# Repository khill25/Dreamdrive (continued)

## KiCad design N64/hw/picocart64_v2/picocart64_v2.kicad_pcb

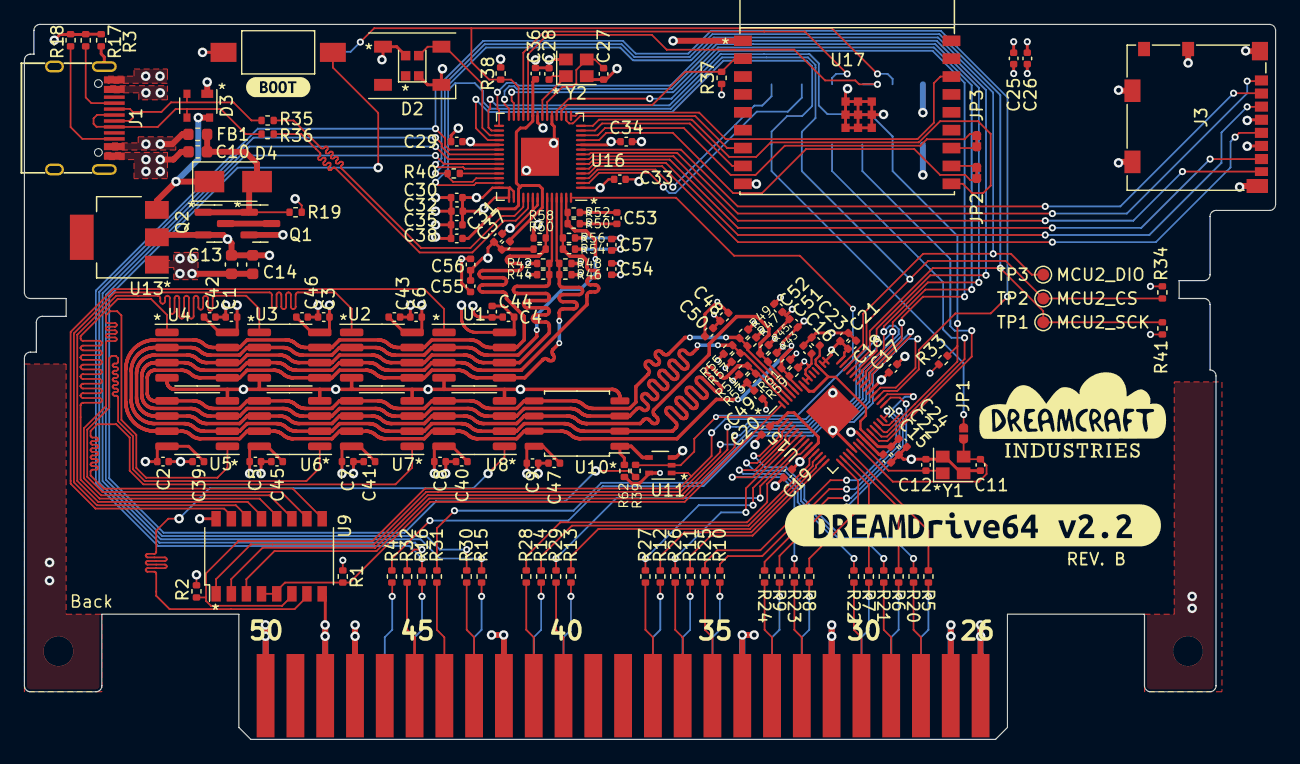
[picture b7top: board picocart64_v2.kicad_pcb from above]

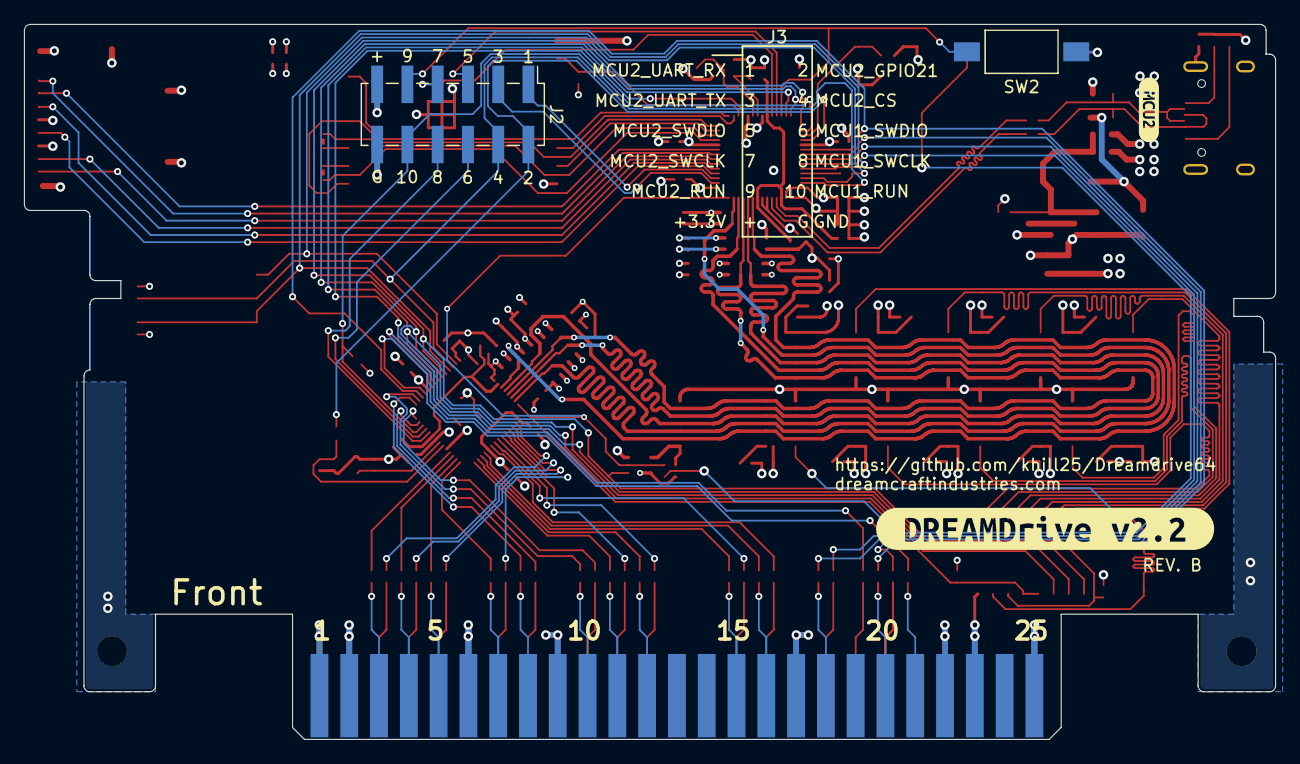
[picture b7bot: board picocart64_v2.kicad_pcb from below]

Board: 4 copper layers, 105.0 x 60.0 mm, 159 parts (5 on the bottom side), 121 nets.

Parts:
C1, C2, C3, C4, C5, C6, C7, C8, C9, C15, C16, C17, C18, C19, C20, C22, C23, C26, C29, C30, C31, C32, C33, C34, C36, C37, C48, C49, C50, C51, C52, C53, C54, C55, C56, C57: 100n; C_0402_1005Metric
C10, C13, C14: 10u; C_0603_1608Metric
C11, C12, C27, C28: 12p; C_0402_1005Metric
C21, C24, C25, C35, C38, C39, C40, C41, C42, C43, C44, C45, C46, C47: 1u; C_0402_1005Metric
D1: WS2812B-2020
D2: WS2812B; LED_WS2812B_PLCC4_5.0x5.0mm_P3.2mm
D3: DRTR5V0U2SR-7; SOT-143
D4: D_Small; D_SMA
FB1: Ferrite; L_0603_1608Metric
J1: USB_C_Receptacle_USB2.0; USB_C_Receptacle_GT-USB-7010
J2: Conn_02x06_Odd_Even; PinHeader_2x06_P2.54mm_Vertical_SMD
J3: Micro_SD_Card_Det; microSD_HC_Molex_104031-0811
JP1: SolderJumper_2_Open; SolderJumper-2_Small_Open
JP2, JP3: SolderJumper_2_Bridged; SolderJumper-2_Small_Closed
Q1, Q2: FDN340P; SOT-23
R1, R2, R33, R34, R62: 10K; R_0402_1005Metric
R3: 100k; R_0402_1005Metric
R4, R5, R6, R7, R8, R9, R10, R11, R12, R13, R14, R15, R16, R20, R21, R22, R23, R24, R25, R26, R27, R28, R29, R30, R31, R32, R35, R36: 22R; R_0402_1005Metric
R17, R18: 5k1; R_0402_1005Metric
R19, R37, R38, R41: 10k; R_0402_1005Metric
R39: 1K; R_0402_1005Metric
R40: 470R; R_0402_1005Metric
R42, R43, R44, R45, R46, R47, R48, R49, R50, R51, R52, R53, R54, R55, R56, R57, R58, R59, R60, R61: R; R_0402_1005Metric
SW1: BootButton; SW_SPST_FSMSM
SW2: ResetButton; SW_SPST_FSMSM
TP1: TP_MCU2_SCK; TestPoint_Pad_D1.0mm
TP2: TP_MCU2_CS; TestPoint_Pad_D1.0mm
TP3: TP_MCU2_DIO; TestPoint_Pad_D1.0mm
U1, U2, U3, U4, U5, U6, U7, U8: APS6404L-3SQR; SOP-8_3.76x4.96mm_P1.27mm
U9: SN74LVC138AQDRQ1; SOP-16_4.4x10.4mm_P1.27mm
U10: W25Q128JVS; SOIC-8_5.23x5.23mm_P1.27mm
U11: 74LVC1G125GW; SOT-353_SC-70-5
U13: AZ1117-3.3; SOT-223
U14: N64-Cartridge; N64-Connector
U15, U16: RP2040; QFN-56_EP_7x7_Pitch0.4mm
U17: ESP32-C3-WROOM-02
Y1, Y2: 12MHz 10ppm; Crystal_SMD_2520-4Pin_2.5x2.0mm
kibuzzard-62F8E97D: G***; kibuzzard-62F8E97D
kibuzzard-62F95F09: G***; kibuzzard-62F95F09
kibuzzard-63B14A32: G***; kibuzzard-63B14A32
kibuzzard-63B14B13: G***; kibuzzard-63B14B13

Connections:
+3V3: C1.1, C2.1, C3.1, C4.1, C5.1, C6.1, C7.1, C8.1, C9.1, C13.1, C14.1, C15.1, C16.1, C17.1, C18.1, C19.1, C20.1, C21.1, C25.1, C26.1, C29.1, C30.1, C31.1, C32.1, C33.1, C34.1, C35.1, C39.1, C40.1, C41.1, C42.1, C43.1, C44.1, C45.1, C46.1, C47.1, C48.1, C49.1, C50.1, C51.1, C52.1, C53.1, C54.1, C55.1, C56.1, C57.1, D1.4 (VDD), D2.1 (VDD), J2.11, J3.4 (VDD), Q2.2 (S), R1.1, R34.2, R38.1, R41.1, R42.2, R43.2, R46.2, R47.2, R50.2, R51.2, R54.2, R55.2, R58.2, R59.2, R62.2, U1.8 (VCC), U2.8 (VCC), U3.8 (VCC), U4.8 (VCC), U5.8 (VCC), U6.8 (VCC), U7.8 (VCC), U8.8 (VCC), U9.16 (VCC), U10.8 (VCC), U11.5 (VCC), U13.2 (VO), U15.1 (IOVDD), U15.10 (IOVDD), U15.22 (IOVDD), U15.33 (IOVDD), U15.42 (IOVDD), U15.43 (ADC_AVDD), U15.44 (VREG_VIN), U15.48 (USB_VDD), U15.49 (IOVDD), U16.1 (IOVDD), U16.10 (IOVDD), U16.22 (IOVDD), U16.33 (IOVDD), U16.42 (IOVDD), U16.43 (ADC_AVDD), U16.44 (VREG_VIN), U16.48 (USB_VDD), U16.49 (IOVDD), U17.1 (3V3)
/Mainboard/AD0: R20.2, U15.2 (GPIO0)
/Mainboard/AD0': R20.1, U14.28 (AD0)
/Mainboard/AD1: R21.2, U15.3 (GPIO1)
/Mainboard/AD1': R21.1, U14.29 (AD1)
/Mainboard/AD2: R22.2, U15.4 (GPIO2)
/Mainboard/AD2': R22.1, U14.30 (AD2)
/Mainboard/AD3: R23.2, U15.5 (GPIO3)
/Mainboard/AD3': R23.1, U14.32 (AD3)
/Mainboard/AD4: R26.2, U15.6 (GPIO4)
/Mainboard/AD4': R26.1, U14.36 (AD4)
/Mainboard/AD5: R27.2, U15.7 (GPIO5)
/Mainboard/AD5': R27.1, U14.37 (AD5)
/Mainboard/AD6: R29.2, U15.8 (GPIO6)
/Mainboard/AD6': R29.1, U14.40 (AD6)
/Mainboard/AD7: R28.2, U15.9 (GPIO7)
/Mainboard/AD7': R28.1, U14.41 (AD7)
/Mainboard/AD8: R14.1, U15.11 (GPIO8)
/Mainboard/AD8': R14.2, U14.16 (AD8)
/Mainboard/AD9: R13.1, U15.12 (GPIO9)
/Mainboard/AD9': R13.2, U14.15 (AD9)
/Mainboard/AD10: R12.1, U15.13 (GPIO10)
/Mainboard/AD10': R12.2, U14.12 (AD10)
/Mainboard/AD11: R11.1, U15.14 (GPIO11)
/Mainboard/AD11': R11.2, U14.11 (AD11)
/Mainboard/AD12: R8.1, U15.15 (GPIO12)
/Mainboard/AD12': R8.2, U14.7 (AD12)
/Mainboard/AD13: R7.1, U15.16 (GPIO13)
/Mainboard/AD13': R7.2, U14.5 (AD13)
/Mainboard/AD14: R6.1, U15.17 (GPIO14)
/Mainboard/AD14': R6.2, U14.4 (AD14)
/Mainboard/AD15: R5.1, U15.18 (GPIO15)
/Mainboard/AD15': R5.2, U14.3 (AD15)
/Mainboard/ALEH: R25.2, U15.28 (GPIO17)
/Mainboard/ALEH': R25.1, U14.35 (ALEH)
/Mainboard/ALEL: R24.2, U15.27 (GPIO16)
/Mainboard/ALEL': R24.1, U14.33 (ALEL)
/Mainboard/CIC_DCLK: R30.2, U16.37 (GPIO25)
/Mainboard/CIC_DCLK': R30.1, U14.43 (CIC_DCLK)
/Mainboard/CIC_DIO: R15.1, U16.36 (GPIO24)
/Mainboard/CIC_DIO': R15.2, U14.18 (CIC_DIO)
/Mainboard/DEMUX_A0: U9.1 (A0), U15.35 (GPIO23), U16.18 (GPIO15)
/Mainboard/DEMUX_A1: U9.2 (A1), U15.36 (GPIO24), U16.27 (GPIO16)
/Mainboard/DEMUX_A2: U9.3 (A2), U15.37 (GPIO25), U16.28 (GPIO17)
/Mainboard/DEMUX_IE: R2.2, U9.6 (E3), U11.1 (~OE), U15.38 (GPIO26), U16.29 (GPIO18)
/Mainboard/ESP32_CS: U16.15 (GPIO12), U17.16 (GPIO2/ADC1_CH2)
/Mainboard/ESP32_D0_TX: JP2.2 (B), U16.11 (GPIO8)
/Mainboard/ESP32_D1_RX: JP3.2 (B), U16.12 (GPIO9)
/Mainboard/ESP32_D2_G9: U16.13 (GPIO10), U17.8 (GPIO9)
/Mainboard/ESP32_D3: U16.14 (GPIO11), U17.10 (GPIO10)
/Mainboard/ESP32_EN: R37.2, U16.17 (GPIO14), U17.2 (EN/CHIP_PU)
/Mainboard/ESP32_SCK: U16.16 (GPIO13), U17.7 (GPIO8)
/Mainboard/LED: D1.3 (DIN), D2.4 (DIN), U16.31 (GPIO20)
/Mainboard/MCU1_RUN: J2.10, R33.2, U15.26 (RUN), U16.30 (GPIO19)
/Mainboard/MCU1_SWCLK: J2.8, U15.24 (SWCLK)
/Mainboard/MCU1_SWDIO: J2.6, U15.25 (SWDIO)
/Mainboard/MCU1_XIN: C11.2, JP1.2 (B), U15.20 (XIN), Y1.3
/Mainboard/MCU1_XOUT: C12.2, U15.21 (XOUT), Y1.1
/Mainboard/MCU2_CS: J2.4, R34.1, TP2.1, U15.40 (GPIO28), U16.41 (GPIO29)
/Mainboard/MCU2_DIO: R40.2, TP3.1, U15.41 (GPIO29), U16.40 (GPIO28)
/Mainboard/MCU2_G27: R40.1, U16.39 (GPIO27)
/Mainboard/MCU2_GPIO21: J2.2, JP1.1 (A), U16.32 (GPIO21)
/Mainboard/MCU2_RUN: J2.9, R38.2, SW2.1, U16.26 (RUN)
/Mainboard/MCU2_SCK: R41.2, TP1.1, U15.39 (GPIO27), U16.38 (GPIO26)
/Mainboard/MCU2_SWCLK: J2.7, U16.24 (SWCLK)
/Mainboard/MCU2_SWDIO: J2.5, U16.25 (SWDIO)
/Mainboard/MCU2_UART_RX: J2.1, U16.3 (GPIO1)
/Mainboard/MCU2_UART_TX: J2.3, U16.2 (GPIO0)
/Mainboard/MCU2_USB_D+: D3.3 (I/O2), J1.A6 (D+), J1.B6 (D+), R36.1
/Mainboard/MCU2_USB_D-: D3.2 (I/O1), J1.A7 (D-), J1.B7 (D-), R35.1
/Mainboard/MCU2_XIN: C27.2, U16.20 (XIN), Y2.3
/Mainboard/MCU2_XOUT: C28.2, U16.21 (XOUT), Y2.1
/Mainboard/N64_VCC: Q1.2 (S), U14.9 (VCC), U14.17 (VCC), U14.34 (VCC), U14.42 (VCC)
/Mainboard/SD_CLK: J3.5 (CLK), U16.4 (GPIO2)
/Mainboard/SD_CMD: J3.3 (CMD), U16.5 (GPIO3)
/Mainboard/SD_DAT0: J3.7 (DAT0), U16.6 (GPIO4)
/Mainboard/SD_DAT1: J3.8 (DAT1), U16.7 (GPIO5)
/Mainboard/SD_DAT2: J3.1 (DAT2), U16.8 (GPIO6)
/Mainboard/SD_DAT3: J3.2 (DAT3/CD), U16.9 (GPIO7)
/Mainboard/SI_DAT: R4.1, U15.32 (GPIO21)
/Mainboard/SI_DAT': R4.2, U14.21 (SI_DAT)
/Mainboard/SSI_SCLK: R42.1, R43.1, R44.2, R45.2, U1.6 (SCLK), U2.6 (SCLK), U3.6 (SCLK), U4.6 (SCLK), U5.6 (SCLK), U6.6 (SCLK), U7.6 (SCLK), U8.6 (SCLK), U10.6 (CLK), U15.52 (QSPI_SCLK), U16.52 (QSPI_SCLK)
/Mainboard/SSI_SD0: R46.1, R47.1, R48.2, R49.2, U1.5 (SI/SIO), U2.5 (SI/SIO), U3.5 (SI/SIO), U4.5 (SI/SIO), U5.5 (SI/SIO), U6.5 (SI/SIO), U7.5 (SI/SIO), U8.5 (SI/SIO), U10.5 (DI(IO0)), U15.53 (QSPI_SD0), U16.53 (QSPI_SD0)
/Mainboard/SSI_SD1: R50.1, R51.1, R52.2, R53.2, U1.2 (SO/SIO), U2.2 (SO/SIO), U3.2 (SO/SIO), U4.2 (SO/SIO), U5.2 (SO/SIO), U6.2 (SO/SIO), U7.2 (SO/SIO), U8.2 (SO/SIO), U10.2 (DO(IO1)), U15.55 (QSPI_SD1), U16.55 (QSPI_SD1)
/Mainboard/SSI_SD2: R54.1, R55.1, R56.2, R57.2, U1.3 (SIO2), U2.3 (SIO2), U3.3 (SIO2), U4.3 (SIO2), U5.3 (SIO2), U6.3 (SIO2), U7.3 (SIO2), U8.3 (SIO2), U10.3 (IO2), U15.54 (QSPI_SD2), U16.54 (QSPI_SD2)
/Mainboard/SSI_SD3: R58.1, R59.1, R60.2, R61.2, U1.7 (SIO3), U2.7 (SIO3), U3.7 (SIO3), U4.7 (SIO3), U5.7 (SIO3), U6.7 (SIO3), U7.7 (SIO3), U8.7 (SIO3), U10.7 (IO3), U15.51 (QSPI_SD3), U16.51 (QSPI_SD3)
/Mainboard/VBUS': FB1.1, J1.A4 (VBUS), J1.A9 (VBUS), J1.B4 (VBUS), J1.B9 (VBUS)
/Mainboard/~COLD_RESET': R16.2, U14.20 (~COLD_RESET)
/Mainboard/~COLD_RESET: R16.1, U15.31 (GPIO20), U16.34 (GPIO22)
/Mainboard/~INT1': R31.1, U14.44 (~INT1)
/Mainboard/~INT1: R31.2, U15.34 (GPIO22)
/Mainboard/~NMI': R32.1, U14.45 (~NMI)
/Mainboard/~NMI: R32.2, U16.35 (GPIO23)
/Mainboard/~READ': R10.2, U14.10 (~READ)
/Mainboard/~READ: R10.1, U15.30 (GPIO19)
/Mainboard/~WRITE': R9.2, U14.8 (~WRITE)
/Mainboard/~WRITE: R9.1, U15.29 (GPIO18)
/PSRAM Array/CS1: U1.1 (~CE), U9.15 (O0)
/PSRAM Array/CS2: U2.1 (~CE), U9.14 (O1)
/PSRAM Array/CS3: U3.1 (~CE), U9.13 (O2)
/PSRAM Array/CS4: U4.1 (~CE), U9.12 (O3)
/PSRAM Array/CS5: U5.1 (~CE), U9.11 (O4)
/PSRAM Array/CS6: U6.1 (~CE), U9.10 (O5)
/PSRAM Array/CS7: U7.1 (~CE), U9.9 (O6)
/PSRAM Array/CS8: U8.1 (~CE), U9.7 (O7)
/PSRAM Array/CSBOOT: R62.1, U10.1 (~CS), U11.4 (Y)
GND: C1.2, C2.2, C3.2, C4.2, C5.2, C6.2, C7.2, C8.2, C9.2, C10.2, C11.1, C12.1, C13.2, C14.2, C15.2, C16.2, C17.2, C18.2, C19.2, C20.2, C21.2, C22.2, C23.2, C24.2, C25.2, C26.2, C27.1, C28.1, C29.2, C30.2, C31.2, C32.2, C33.2, C34.2, C35.2, C36.2, C37.2, C38.2, C39.2, C40.2, C41.2, C42.2, C43.2, C44.2, C45.2, C46.2, C47.2, C48.2, C49.2, C50.2, C51.2, C52.2, C53.2, C54.2, C55.2, C56.2, C57.2, D1.2 (VSS), D2.3 (VSS), D3.1 (GND), J1.A1 (GND), J1.A12 (GND), J1.B1 (GND), J1.B12 (GND), J2.12, J3.6 (VSS), J3.9 (DET_B), J3.11 (SHIELD), R2.1, R3.1, R17.2, R18.2, R19.1, R33.1, R37.1, R44.1, R45.1, R48.1, R49.1, R52.1, R53.1, R56.1, R57.1, R60.1, R61.1, SW1.2, SW2.2, U1.4 (VSS), U2.4 (VSS), U3.4 (VSS), U4.4 (VSS), U5.4 (VSS), U6.4 (VSS), U7.4 (VSS), U8.4 (VSS), U9.8 (GND), U10.4 (GND), U11.3 (GND), U13.1 (GND), U14.1 (GND), U14.2 (GND), U14.6 (GND), U14.22 (GND), U14.23 (GND), U14.25 (GND), U14.26 (GND), U14.27 (GND), U14.31 (GND), U14.47 (GND), U14.48 (GND), U14.50 (GND), U15.19 (TESTEN), U15.57 (GND), U16.19 (TESTEN), U16.57 (GND), U17.9 (GND), U17.19 (GND), Y1.2, Y1.4, Y2.2, Y2.4
unnamed: C22.1, C23.1, C24.1, U15.23 (DVDD), U15.45 (VREG_VOUT), U15.50 (DVDD)
unnamed: C36.1, C37.1, C38.1, U16.23 (DVDD), U16.45 (VREG_VOUT), U16.50 (DVDD)
unnamed: D3.4 (VCC), D4.1 (K), U13.3 (VI)
unnamed: J1.A5 (CC1), R17.1
unnamed: J1.B5 (CC2), R18.1
unnamed: J1.S1 (SHIELD), R3.2
unnamed: JP2.1 (A), U17.11 (GPIO20/U0RXD)
unnamed: JP3.1 (A), U17.12 (GPIO21/U0TXD)
unnamed: Q1.3 (D), Q2.3 (D)
unnamed: R35.2, U16.46 (USB_D-)
unnamed: R36.2, U16.47 (USB_D+)
unnamed: R39.2, SW1.1
VBUS: C10.1, D4.2 (A), FB1.2, Q1.1 (G), Q2.1 (G), R19.2
~SSI_CS: R1.2, R39.1, U9.4 (E1), U9.5 (E2), U11.2 (A), U15.56 (~QSPI_CS), U16.56 (~QSPI_CS)

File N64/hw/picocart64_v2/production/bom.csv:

Designator,Footprint,Quantity,Value,LCSC Part #
C37,C_0402_1005Metric,1,100n,C147639
C40,C_0402_1005Metric,1,1u,
R62,R_0402_1005Metric,1,10K,
R33,R_0402_1005Metric,1,10K,
C4,C_0402_1005Metric,1,100n,C147639
R45,R_0402_1005Metric,1,R,C105637
C3,C_0402_1005Metric,1,100n,
TP1,TestPoint_Pad_D1.0mm,1,TP_MCU2_SCK,
R29,R_0402_1005Metric,1,22R,
U7,SOP-8_3.76x4.96mm_P1.27mm,1,APS6404L-3SQR,
C5,C_0402_1005Metric,1,100n,
R42,R_0402_1005Metric,1,R,C105637
C32,C_0402_1005Metric,1,100n,C147639
R17,R_0402_1005Metric,1,5k1,
C16,C_0402_1005Metric,1,100n,C147639
C28,C_0402_1005Metric,1,12p,
R21,R_0402_1005Metric,1,22R,
C39,C_0402_1005Metric,1,1u,
R37,R_0402_1005Metric,1,10k,
U8,SOP-8_3.76x4.96mm_P1.27mm,1,APS6404L-3SQR,
TP2,TestPoint_Pad_D1.0mm,1,TP_MCU2_CS,
R24,R_0402_1005Metric,1,22R,
C19,C_0402_1005Metric,1,100n,C147639
C8,C_0402_1005Metric,1,100n,C147639
R43,R_0402_1005Metric,1,R,C105637
U1,SOP-8_3.76x4.96mm_P1.27mm,1,APS6404L-3SQR,
C54,C_0402_1005Metric,1,100n,C147639
C10,C_0603_1608Metric,1,10u,
C12,C_0402_1005Metric,1,12p,
D1,WS2812B-2020,1,WS2812B-2020,
U16,QFN-56_EP_7x7_Pitch0.4mm,1,RP2040,
JP2,SolderJumper-2_Small_Closed,1,SolderJumper_2_Bridged,
C36,C_0402_1005Metric,1,100n,C147639
R30,R_0402_1005Metric,1,22R,
R54,R_0402_1005Metric,1,R,C105637
U15,QFN-56_EP_7x7_Pitch0.4mm,1,RP2040,
C47,C_0402_1005Metric,1,1u,
Y2,Crystal_SMD_2520-4Pin_2.5x2.0mm,1,12MHz 10ppm,C521567
FB1,L_0603_1608Metric,1,Ferrite,
R48,R_0402_1005Metric,1,R,C105637
C38,C_0402_1005Metric,1,1u,
Y1,Crystal_SMD_2520-4Pin_2.5x2.0mm,1,12MHz 10ppm,C521567
R20,R_0402_1005Metric,1,22R,
U6,SOP-8_3.76x4.96mm_P1.27mm,1,APS6404L-3SQR,
U5,SOP-8_3.76x4.96mm_P1.27mm,1,APS6404L-3SQR,
R50,R_0402_1005Metric,1,R,C105637
R56,R_0402_1005Metric,1,R,C105637
R2,R_0402_1005Metric,1,10K,
R26,R_0402_1005Metric,1,22R,
J1,USB_C_Receptacle_GT-USB-7010,1,USB_C_Receptacle_USB2.0,
C31,C_0402_1005Metric,1,100n,C147639
C2,C_0402_1005Metric,1,100n,C147639
U2,SOP-8_3.76x4.96mm_P1.27mm,1,APS6404L-3SQR,
C30,C_0402_1005Metric,1,100n,C147639
U9,SOP-16_4.4x10.4mm_P1.27mm,1,SN74LVC138AQDRQ1,
SW1,SW_SPST_FSMSM,1,BootButton,
R41,R_0402_1005Metric,1,10k,
U10,SOIC-8_5.23x5.23mm_P1.27mm,1,W25Q128JVS,
R31,R_0402_1005Metric,1,22R,
C9,C_0402_1005Metric,1,100n,C147639
R10,R_0402_1005Metric,1,22R,
C52,C_0402_1005Metric,1,100n,C147639
C11,C_0402_1005Metric,1,12p,
J3,microSD_HC_Molex_104031-0811,1,Micro_SD_Card_Det,
U13,SOT-223,1,AZ1117-3.3,
R59,R_0402_1005Metric,1,R,C105637
R5,R_0402_1005Metric,1,22R,
R53,R_0402_1005Metric,1,R,C105637
R15,R_0402_1005Metric,1,22R,
C44,C_0402_1005Metric,1,1u,
C7,C_0402_1005Metric,1,100n,
C18,C_0402_1005Metric,1,100n,C147639
C24,C_0402_1005Metric,1,1u,
Q2,SOT-23,1,FDN340P,C347510
R12,R_0402_1005Metric,1,22R,
C41,C_0402_1005Metric,1,1u,
R19,R_0402_1005Metric,1,10k,
TP3,TestPoint_Pad_D1.0mm,1,TP_MCU2_DIO,
U11,SOT-353_SC-70-5,1,74LVC1G125GW,
R6,R_0402_1005Metric,1,22R,
JP1,SolderJumper-2_Small_Open,1,SolderJumper_2_Open,
D2,LED_WS2812B_PLCC4_5.0x5.0mm_P3.2mm,1,WS2812B,WS2812B-2020
R44,R_0402_1005Metric,1,R,C105637
C50,C_0402_1005Metric,1,100n,C147639
C45,C_0402_1005Metric,1,1u,
R25,R_0402_1005Metric,1,22R,
Q1,SOT-23,1,FDN340P,C347510
R39,R_0402_1005Metric,1,1K,
C57,C_0402_1005Metric,1,100n,C147639
U17,ESP32-C3-WROOM-02,1,ESP32-C3-WROOM-02,
C51,C_0402_1005Metric,1,100n,C147639
R4,R_0402_1005Metric,1,22R,
C20,C_0402_1005Metric,1,100n,C147639
C1,C_0402_1005Metric,1,100n,C147639
R27,R_0402_1005Metric,1,22R,
C6,C_0402_1005Metric,1,100n,C147639
R1,R_0402_1005Metric,1,10K,
R58,R_0402_1005Metric,1,R,C105637
C42,C_0402_1005Metric,1,1u,
C13,C_0603_1608Metric,1,10u,
C49,C_0402_1005Metric,1,100n,C147639
C33,C_0402_1005Metric,1,100n,C147639
R18,R_0402_1005Metric,1,5k1,
R36,R_0402_1005Metric,1,22R,
C56,C_0402_1005Metric,1,100n,C147639
C27,C_0402_1005Metric,1,12p,
R13,R_0402_1005Metric,1,22R,
C26,C_0402_1005Metric,1,100n,C147639
R34,R_0402_1005Metric,1,10K,
R3,R_0402_1005Metric,1,100k,
D3,SOT-143,1,DRTR5V0U2SR-7,C443828
R28,R_0402_1005Metric,1,22R,
R47,R_0402_1005Metric,1,R,C105637
C22,C_0402_1005Metric,1,100n,C147639
R46,R_0402_1005Metric,1,R,C105637
R38,R_0402_1005Metric,1,10k,
R52,R_0402_1005Metric,1,R,C105637
R8,R_0402_1005Metric,1,22R,
C21,C_0402_1005Metric,1,1u,
D4,D_SMA,1,D_Small,C22452
C43,C_0402_1005Metric,1,1u,
U3,SOP-8_3.76x4.96mm_P1.27mm,1,APS6404L-3SQR,
C14,C_0603_1608Metric,1,10u,
R51,R_0402_1005Metric,1,R,C105637
R32,R_0402_1005Metric,1,22R,
JP3,SolderJumper-2_Small_Closed,1,SolderJumper_2_Bridged,
R61,R_0402_1005Metric,1,R,C105637
C29,C_0402_1005Metric,1,100n,C147639
R16,R_0402_1005Metric,1,22R,
C35,C_0402_1005Metric,1,1u,
C48,C_0402_1005Metric,1,100n,C147639
C34,C_0402_1005Metric,1,100n,C147639
C55,C_0402_1005Metric,1,100n,C147639
R7,R_0402_1005Metric,1,22R,
C17,C_0402_1005Metric,1,100n,C147639
R9,R_0402_1005Metric,1,22R,
R49,R_0402_1005Metric,1,R,C105637
R57,R_0402_1005Metric,1,R,C105637
U4,SOP-8_3.76x4.96mm_P1.27mm,1,APS6404L-3SQR,
C23,C_0402_1005Metric,1,100n,C147639
R35,R_0402_1005Metric,1,22R,
R14,R_0402_1005Metric,1,22R,
R60,R_0402_1005Metric,1,R,C105637
R40,R_0402_1005Metric,1,470R,
R22,R_0402_1005Metric,1,22R,
C25,C_0402_1005Metric,1,1u,
C46,C_0402_1005Metric,1,1u,
C53,C_0402_1005Metric,1,100n,C147639
C15,C_0402_1005Metric,1,100n,C147639
R11,R_0402_1005Metric,1,22R,
R55,R_0402_1005Metric,1,R,C105637
R23,R_0402_1005Metric,1,22R,
U14,N64-Connector,1,N64-Cartridge,
J2,PinHeader_2x06_P2.54mm_Vertical_SMD,1,Conn_02x06_Odd_Even,
SW2,SW_SPST_FSMSM,1,ResetButton,

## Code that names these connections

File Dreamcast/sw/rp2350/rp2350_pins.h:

/**
 * SPDX-License-Identifier: BSD-2-Clause
 *
 * Copyright (c) 2023 Kaili Hill
 */

#pragma once

#define DATABUS_D0 0  // D0-D15 on GPIO 0-15
#define PIN_A0 16
#define PIN_A1 17
#define PIN_A2 18
#define PIN_CS0 19
#define PIN_CS1 20
#define PIN_RD 21
#define PIN_WR 22
#define PIN_IORDY 23
#define PIN_INTRQ 24
#define PIN_DMARQ 25
#define PIN_DMACK 26
#define PIN_CD_LRCK 27
#define PIN_CD_BCK 28
#define PIN_CD_SDAT 29
#define PIN_CDDA_CLK 30
#define PIN_CD_EMPH 31
#define PIN_DOPEN 32
#define PIN_GD_RST 33
#define PIN_SD_CLK 34
#define PIN_SD_CMD 35
#define PIN_SD_D0 36
#define PIN_SD_D1 37
#define PIN_SD_D2 38
#define PIN_SD_D3 39

// Update masks for the new pin layout
#define CS_PINS_MASK (0x18)
#define READ_WRITE_PIN_MASK (0x60)
#define READ_PIN_MASK (0x40)
#define WRITE_PIN_MASK (0x20)
#define REGISTER_PIN_MASK (0x7F)
#define BIT_SHIFTED_READ_PIN_MASK (0x40)

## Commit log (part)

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2023-02-16 Added start of dreamcast gdrom breakout board.
2023-02-16 Updating dreamcast schematic with lots of notes about what signals are used for what.
2023-02-17 More notes about how the dreamcast gdrom protocol works and what the pins do
2023-02-17 Save?
2023-02-17 Updated dreamcast schematic and created a PDF version.
2023-02-17 Ignore the backup folder. AND also check in the changes to the schematic.
2023-02-18 Routed dreamcast board. Added some footprints and symbols for the molex connector.
2023-02-22 Updated PCB with artwork and production files. Rotations still seem off sometimes when I import them into JLCPCB although they seem to be able to assemble the boards just fine.
2023-03-09 Adding some basic structure for dreamcast firmware
2023-03-28 Moved source code from PicoCart64 fork to its own repo here.
2023-03-28 Moved serial bridge to shared folder
2023-04-02 TX waits until RX has sampled data before continuing.
2023-04-02 Fixed more dead lock issues. This code can get out of sync and the bits can be shifted into the wrong place.
    Probably want to use flags to sample 16bits instead of 4.
2023-04-02 Cleanup some comments and unused code. MCU2 test now sends 16 half words, 10 ms apart, then waits 500ms before doing another burst.
2023-04-11 Adding in contents about how the Sega Packet Interface works.
2023-04-12 Lots of docs and started writing out the variables and structs to house the various packet infos
2023-04-12 Updated with more GDROM spec code and comments
2023-04-12 Wrote a lot of code and comments about the processing all these ATA and SPI commands.
2023-04-13 Updated the docs with an updated table from the spi spec pdf since the one in the pdf was wrong (cs0 and cs1 were flipped) Got data flowing to mcu1 when mcu2 sees changes on the control pins. Likely 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
2023-04-15 Moved read/write to MCU1, also only now use 2 data pins for comms.
    Updated some code to account for this change. As well as the fact that the cs0 cs1 lines were reversed.
    Updated some docs for new swapped cs line values
2023-04-15 Trying to get read and write triggering something on mcu1. It doesn't seem fast enough to handle reading the rx buffer after the rd/wr pin goes low. Or at least the mcu2_control_line_state I'm using 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
2023-04-18 Weird rabbit hole of pin low detection latency. Have a working solution that will monitor the 2 CS pins with 1 PIO program each, raise an IRQ which a 3rd program will read and set gpio 18 high (to te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
2023-04-18 Writing out some prototype PIO code that waits for CS lines then read or writes to the bus.
2023-04-21 Update schematic to use rp2040s, mux the control lines with some data pins on mcu1, and change the pinout. PCB hasn't been rerouted yet.
2023-04-21 Updated PCB for new schematic design, still needs to be routed.
2023-04-23 Generated BOM and position files for pcb assembly.
2023-04-23 Wrote some PIO code that might make some sense to jmp to read/write labels and 2 more programs like the CS detect programs, that are used for read and write. Wrote some comments about the setup and q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
2023-04-24 Moved some things around. Wrote a struct to contain all the databus pio programs, should make it easier to swap out the cs detect for read/write detect programs. Still not sure how fast that actually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
2023-05-05 Setup dreamcast sdk and created some files that compile
2023-06-19 Updated some files with new pin outs for the new board revision. Using PIO_UART from dreamdrive64 instead of serial_bridge as we now only have 2 pins and that already works.
2023-07-17 Made some comments about CS1/CS0... Table from the pdf uses 'A' and 'N' and columns in CS0, CS1... Since A=0v[binary 0] and N=3v[binary 1], we can swap the values and use the binary values as is. Thi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
2023-07-28 Switched to using uart output (with a bodge wire soldered on the comms_pio0 via for uart0-tx. Wrote a test to figure out the number of cycles to swap two pio programs and running into some weird issu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
2023-08-04 Rewriting the databus PIO code. Refactoring...
2023-08-04 Trying to get data out of PIO program. It's using the combined CS/RD/WR program that will signal into the datahandler program. Doesn't seem to be pushing anything to the C code. So it is either not s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
2023-12-14 Added some comments to remember how stuff works and working on a new PIO program that won't need to be swapped or manually jmp'd
2023-12-14 More flailing on PIO code to read multiple gpio pins
2023-12-15 Based on wokwi debugging of the PIO code, the cs line detector should work. The databus is still wip but should be good enough to test.
2023-12-15 Clean up code. Add in some best try code to read/write registers Changed data type from uint8_t to uint16_t, not sure if it's even needed but trying to avoid any kind of overflows when assigning valu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
2023-12-15 Change the registers to all be 16 bit and remove the standalone data register. We need to make this as fast as possible.
2023-12-15 TODO look at the main loop and make it look like the wokwi scratch pad. FIXED databus pio. Should properly wait for cs and r/w TODO databus pio might not work correctly if we return quickly after che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
2023-12-15 Think the database pio code is finally sorted. It properly checks the right bits. TODO: It's not waiting for the CS lines to return to 1 before continuing after waiting for the r/w/ lines to go high.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
2023-12-17 Sanity commit before rewriting pio code to use separate state machines for each pin that drops low since the monolithic program doesn't seem to be working correctly. Still unsure if this is an issue 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
2023-12-18 Seems like the MUX chip is data pins active HIGH and control lines active low... I had it backwards... Rewrote the pio programs and it kinda works, I'm at least seeing output but values read from the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
2023-12-27 Hacking up the pio init functions. This isn't really in a runnable state but it also wasn't working either so not really breaking much by moving to initing the programs normally.
2023-12-27 Move to busy waiting for a valid control line config. This seems to work but need more testing to see if it's reliable
2024-06-04 Update dreamdumper board, sanity commit before redoing all routing
2024-06-10 Updated the dreamdumper64 stand alone board. This was submitted for test samples.
    Rewrote a bunch of dreamdrivecast code, it isn't tested but should be a lot faster if it works.
2024-06-11 Still debugging the control line triggering... Checking just the read and write values doesn't eliminate the issue because the CS lines can both be high for some reason.
2024-06-11 This seems to be detecting the correct number of signal transitions as captured in the logic trace. 7... but something else is wrong with maybe my parsing code to decipher the values to registers
2024-06-20 Another sanity commit. Reworking the pio programs in the dreamdrivecast to handle swapping their own pinsdirs
2024-06-20 Check in the pio program file that mcu1 is using to drive an 8bit bus to another rp2040
2024-06-22 Trying with a more complicated solution to flip pindirs in a single pio program on the mux rp2040. Probably need to do the same for the controller rp2040.
2024-06-22 Another attempt at a mux/program that doesn't work.
2024-06-26 Routed another version of the board that includes a bunch of breakout headers. The routing is messing and it needs to have a single power net.
2024-06-27 Update pcb and schematic to reflect diode and removal of second mosfet connected to mcu2
2025-01-21 MIXED COMMIT: Dreamcast related: Data looks like it's flowing correctly! Dreamdrive: Modifed ctr0.s file has been included so others can drop into their pico-sdk folder. Dumper files have been update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
2025-02-19 Finally reading data properly from the dreamcast. Still parsing the complexity of handling all the commands. Need to still process the rest of the packet commands.
2025-02-25 Getting handshake to at least the req_mode command (0x11) but either doesn't like the data or the sector number data is wrong (the disc type and status) or I'm missing something else entirely.
2025-02-25 Turns out code was actually working it just has a long delay after when I normally dump the debug info. Dumping after 60 seconds instead of 18 let us see we are getting a data read command.
2025-02-25 Adding some skeleton for utils classes.
2025-02-26 Culled a bunch of code from nulldc that I wasn't going to be using right now and converted it all to use char instead of wchar. SD card works in SPI mode only. SDIO for pins over 32 need some kind of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
2025-02-28 Renamed c files to cpp to support cpp things. Got a simulated cd_read working from the actual files on the sd card. Data seems to be correct. Need to hook up some of the lower level stuff with signal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
2025-03-04 Dirty hack to keep around the FATFS reference at a project scope so that file references can be used again without issue. Want to look into cleaning this up AND closing unused file handlers. There ar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
2025-03-07 Wrote initial TOC sega packet command implementation. Created a convenience 16bit pointer to the 8bit TOC array for easy writing. NEED TO SET THIS DATA WHILE PROCESSING THE DISC IMAGE!!!
2025-03-09 Load TOC on SPI command.
2025-03-09 Added in ability to store more register reads/writes Debugging CD_READ so there are a few more print statements to determine state. Currently getting stuck sending data to DC with the DC stopping ack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
2025-03-10 Actually apply PatchRegion 0 and 6. Still debugging why the DC stops reading DMA after the first sector (and change, it reads at least a sector but stops somewhere after) Zero out state variables for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
2025-03-11 Saw a command 70 and command 71 come through! So implemented command 71 using nulldc's array values. Removed logging of all reads and writes and only log stuff happening on core1 Trying all kinds of 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
2025-03-11 Refactored the old mai loop to be on core1 in case running our processing loop being on core1 was causing memory issues and prints not working right. This was me misunderstanding what was going on. I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
    Using another approach to command 0x71 (and 0x11) using a rom array I found in another source base.
    Suspect an electrical issue at this point. Depending on how I wiggle it while it's plugged in I may or may not get stuck on a black screen, the sega dreamcast logo, or the dashboard stuck on checking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
2025-03-11 Getting deeper into the rabbit hole. Having chatgpt take a stab at a pio program to handle the ata registers. Or normal code is still getting weird results from the registers access. And the logic an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
2025-03-12 Use DMA with PIO state machines to try and automate the heavy lifting of the ata registers. Busy loop looking for IRQs on reads and writes to alert processing loop.
2025-03-12 The same GPIO can't be used for multiple pios... Figure out a way to condense the programs to fit on one pio?
2025-03-12 Got a PIO program that appears to actually work for ata register stuff... There is something else wrong since the Dreamcast seems stuck unless I power cycle quickly. So check wires and other initial 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
2025-03-12 Refining some issues with the pio code
2025-03-12 Changed how side set worked (the IORDY pin) and I think we might be back to where we were before I decided to rewrite.
2025-03-13 Stable? DC will send command 71 then command 0, then another command 71. It then tries to read the disc but doesn't go beyond that. Very similar to when I fail the 0x11 command challenge where it jus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
2025-03-13 IT LIVES! We get to the sega logo screen!!! This means we have booted the ip.bin section (45150 7 sectors). Need to handle cases where the buffer needs to be reloaded
2025-03-14 Currently after the 5th dma finishes, the ata bus handler loop doesn't ever restart. Debugging while this isn't restarting. Changed the way some setup is handled so we could start and stop the ata ha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
2025-03-15 Trying icegdrom subcode command implementation but that doesn't seem to get me past the "loading crazy taxi (15k)" screen.
2025-03-15 Struggling to get games to load. Soul Calibur loads data but spams the TOC call. Crazy Taxi loads to "loading crazy taxi (15k) screen" and then stalls. Meanwhile it's polling the alt status register 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
2025-03-15 Changed size of gdrom read buffer to be 64 sectors. This is causing a hang(maybe a crash, need to hook up debugger) on the first "big" transfer of 717 sectors. I was using a 16 bit int for num transf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
2025-03-15 ITS WORKS Just need to clean up all the debug info. Next up is getting CDDA working.
2025-03-17 Soul Calibur booting!!!!
